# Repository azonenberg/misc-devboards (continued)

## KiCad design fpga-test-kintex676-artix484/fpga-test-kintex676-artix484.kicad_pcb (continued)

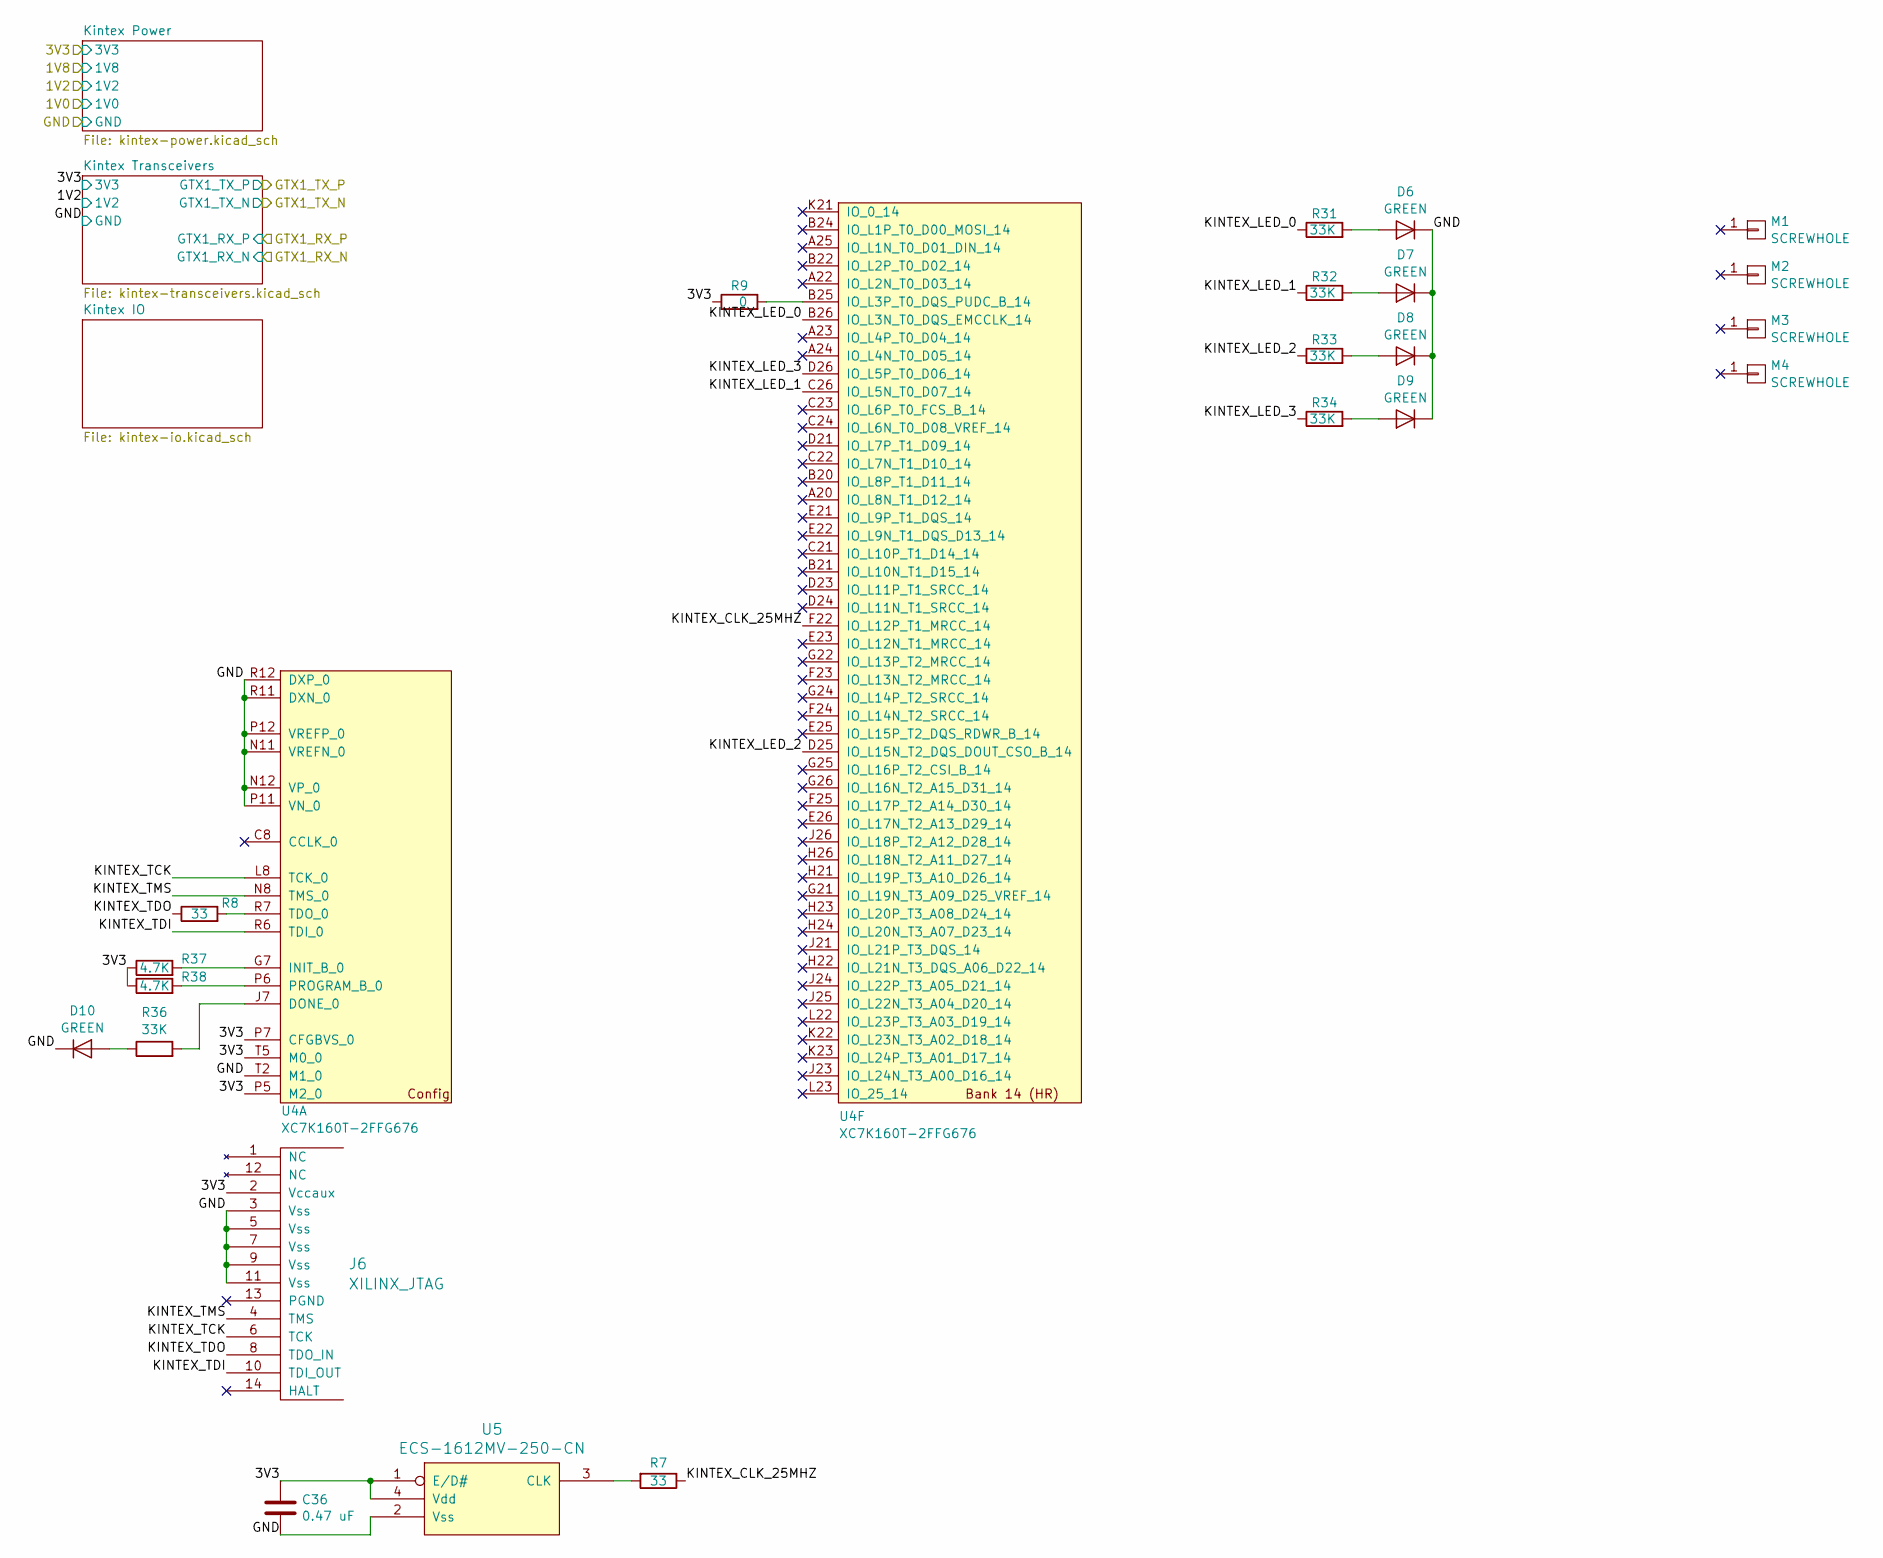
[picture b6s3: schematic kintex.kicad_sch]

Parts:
C36: 0.47 uF; EIA_0402_CAP_NOSILK
D6, D7, D8, D9, D10: GREEN; EIA_0402_LED
J6: XILINX_JTAG; XILINX_JTAG_PTH_MOLEX_0878311420
M1, M2, M3, M4: SCREWHOLE; MECHANICAL_CLEARANCEHOLE_4_40
R7, R8: 33; EIA_0402_RES_NOSILK
R9: 0; EIA_0402_RES_NOSILK
R31, R32, R33, R34, R36: 33K; EIA_0402_RES_NOSILK
R37, R38: 4.7K; EIA_0402_RES_NOSILK
U4: XC7K160T-2FFG676; BGA_676_27x27_FULLARRAY_1MM_FFG676
U5: ECS-1612MV-250-CN; OSCILLATOR_1.6x1.2

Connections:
/GND: C36.2, D6.1 (K), D7.1 (K), D8.1 (K), D9.1 (K), D10.1 (K), J6.3 (Vss), J6.5 (Vss), J6.7 (Vss), J6.9 (Vss), J6.11 (Vss), U4.N11 (VREFN_0), U4.N12 (VP_0), U4.P11 (VN_0), U4.P12 (VREFP_0), U4.R11 (DXN_0), U4.R12 (DXP_0), U4.T2 (M1_0), U5.2 (Vss); also elsewhere on the board
/Kintex FFG676/3V3: C36.1, J6.2 (Vccaux), R9.1, R37.1, R38.1, U4.P5 (M2_0), U4.P7 (CFGBVS_0), U4.T5 (M0_0), U5.1 (E/D#), U5.4 (Vdd); also elsewhere on the board
/Kintex FFG676/KINTEX_CLK_25MHZ: R7.1, U4.F22 (IO_L12P_T1_MRCC_14)
/Kintex FFG676/KINTEX_LED_0: R31.1, U4.B26 (IO_L3N_T0_DQS_EMCCLK_14)
/Kintex FFG676/KINTEX_LED_1: R32.1, U4.C26 (IO_L5N_T0_D07_14)
/Kintex FFG676/KINTEX_LED_2: R33.1, U4.D25 (IO_L15N_T2_DQS_DOUT_CSO_B_14)
/Kintex FFG676/KINTEX_LED_3: R34.1, U4.D26 (IO_L5P_T0_D06_14)
/Kintex FFG676/KINTEX_TCK: J6.6 (TCK), U4.L8 (TCK_0)
/Kintex FFG676/KINTEX_TDI: J6.10 (TDI_OUT), U4.R6 (TDI_0)
/Kintex FFG676/KINTEX_TDO: J6.8 (TDO_IN), R8.1
/Kintex FFG676/KINTEX_TMS: J6.4 (TMS), U4.N8 (TMS_0)
unnamed: D6.2 (A), R31.2
unnamed: D7.2 (A), R32.2
unnamed: D8.2 (A), R33.2
unnamed: D9.2 (A), R34.2
unnamed: D10.2 (A), R36.1
unnamed: R36.2, U4.J7 (DONE_0)
unnamed: R37.2, U4.G7 (INIT_B_0)
unnamed: R38.2, U4.P6 (PROGRAM_B_0)
unnamed: R8.2, U4.R7 (TDO_0)
unnamed: R9.2, U4.B25 (IO_L3P_T0_DQS_PUDC_B_14)
unnamed: R7.2, U5.3 (CLK)

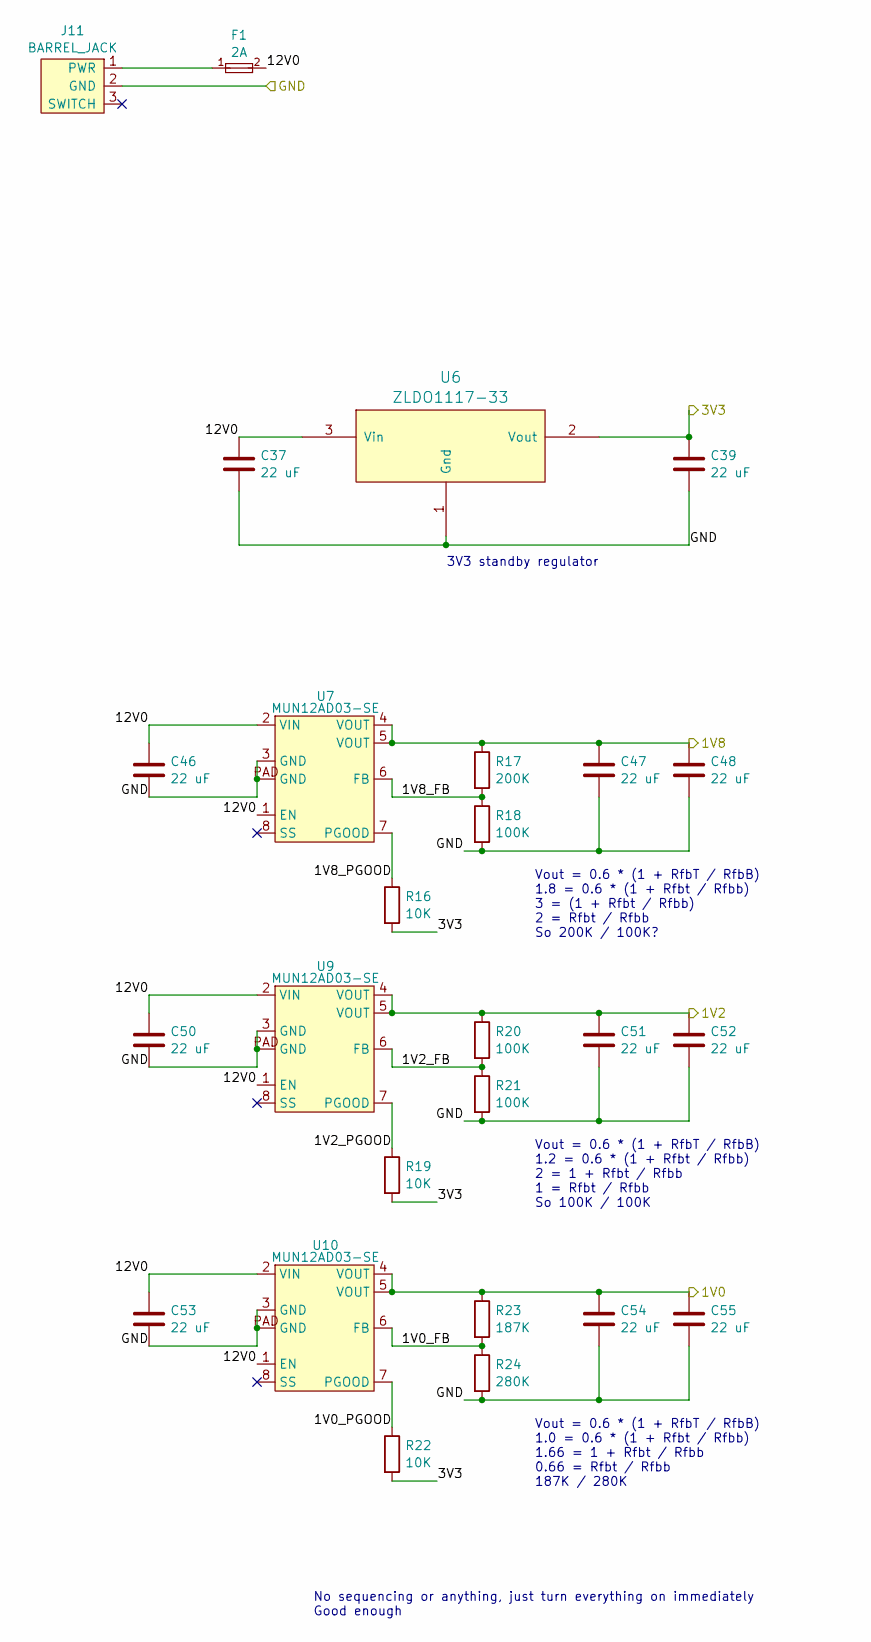
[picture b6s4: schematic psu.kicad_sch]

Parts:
C37, C39, C47, C48, C51, C52, C54, C55: 22 uF; EIA_1210_CAP_NOSILK
C46, C50, C53: 22 uF; EIA_1812_CAP_NOSILK
F1: 2A; EIA_0402_RES_NOSILK
J11: BARREL_JACK; CONN_CUI_PJ-058BH_HIPWR_BARREL_NOSLOT
R16, R19, R22: 10K; EIA_0402_RES_NOSILK
R17: 200K; EIA_0402_RES_NOSILK
R18, R20, R21: 100K; EIA_0402_RES_NOSILK
R23: 187K; EIA_0402_RES_NOSILK
R24: 280K; EIA_0402_RES_NOSILK
U6: ZLDO1117-33; SOT223-4
U7, U9, U10: MUN12AD03-SE; MODULE_CYNTEC_MUN12AD03-SE

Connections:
/1V0: C54.1, C55.1, R23.1, U10.4 (VOUT), U10.5 (VOUT); also elsewhere on the board
/1V2: C51.1, C52.1, R20.1, U9.4 (VOUT), U9.5 (VOUT); also elsewhere on the board
/1V8: C47.1, C48.1, R17.1, U7.4 (VOUT), U7.5 (VOUT); also elsewhere on the board
/3V3: C39.1, R16.2, R19.2, R22.2, U6.2 (Vout); also elsewhere on the board
/GND: C37.2, C39.2, C46.2, C47.2, C48.2, C50.2, C51.2, C52.2, C53.2, C54.2, C55.2, J11.2 (GND), R18.2, R21.2, R24.2, U6.1 (Gnd), U7.3 (GND), U7.PAD (GND), U9.3 (GND), U9.PAD (GND), U10.3 (GND), U10.PAD (GND); also elsewhere on the board
/Power Supply/1V0_FB: R23.2, R24.1, U10.6 (FB)
/Power Supply/1V0_PGOOD: R22.1, U10.7 (PGOOD)
/Power Supply/1V2_FB: R20.2, R21.1, U9.6 (FB)
/Power Supply/1V2_PGOOD: R19.1, U9.7 (PGOOD)
/Power Supply/1V8_FB: R17.2, R18.1, U7.6 (FB)
/Power Supply/1V8_PGOOD: R16.1, U7.7 (PGOOD)
/Power Supply/12V0: C37.1, C46.1, C50.1, C53.1, F1.2, U6.3 (Vin), U7.1 (EN), U7.2 (VIN), U9.1 (EN), U9.2 (VIN), U10.1 (EN), U10.2 (VIN)
unnamed: F1.1, J11.1 (PWR)

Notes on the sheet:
Vout = 0.6 * (1 + RfbT / RfbB) 1.2 = 0.6 * (1 + Rfbt / Rfbb) 2 = 1 + Rfbt / Rfbb 1 = Rfbt / Rfbb So 100K / 100K
Vout = 0.6 * (1 + RfbT / RfbB) 1.8 = 0.6 * (1 + Rfbt / Rfbb) 3 = (1 + Rfbt / Rfbb) 2 = Rfbt / Rfbb So 200K / 100K?
No sequencing or anything, just turn everything on immediately Good enough
3V3 standby regulator
Vout = 0.6 * (1 + RfbT / RfbB) 1.0 = 0.6 * (1 + Rfbt / Rfbb) 1.66 = 1 + Rfbt / Rfbb 0.66 = Rfbt / Rfbb 187K / 280K

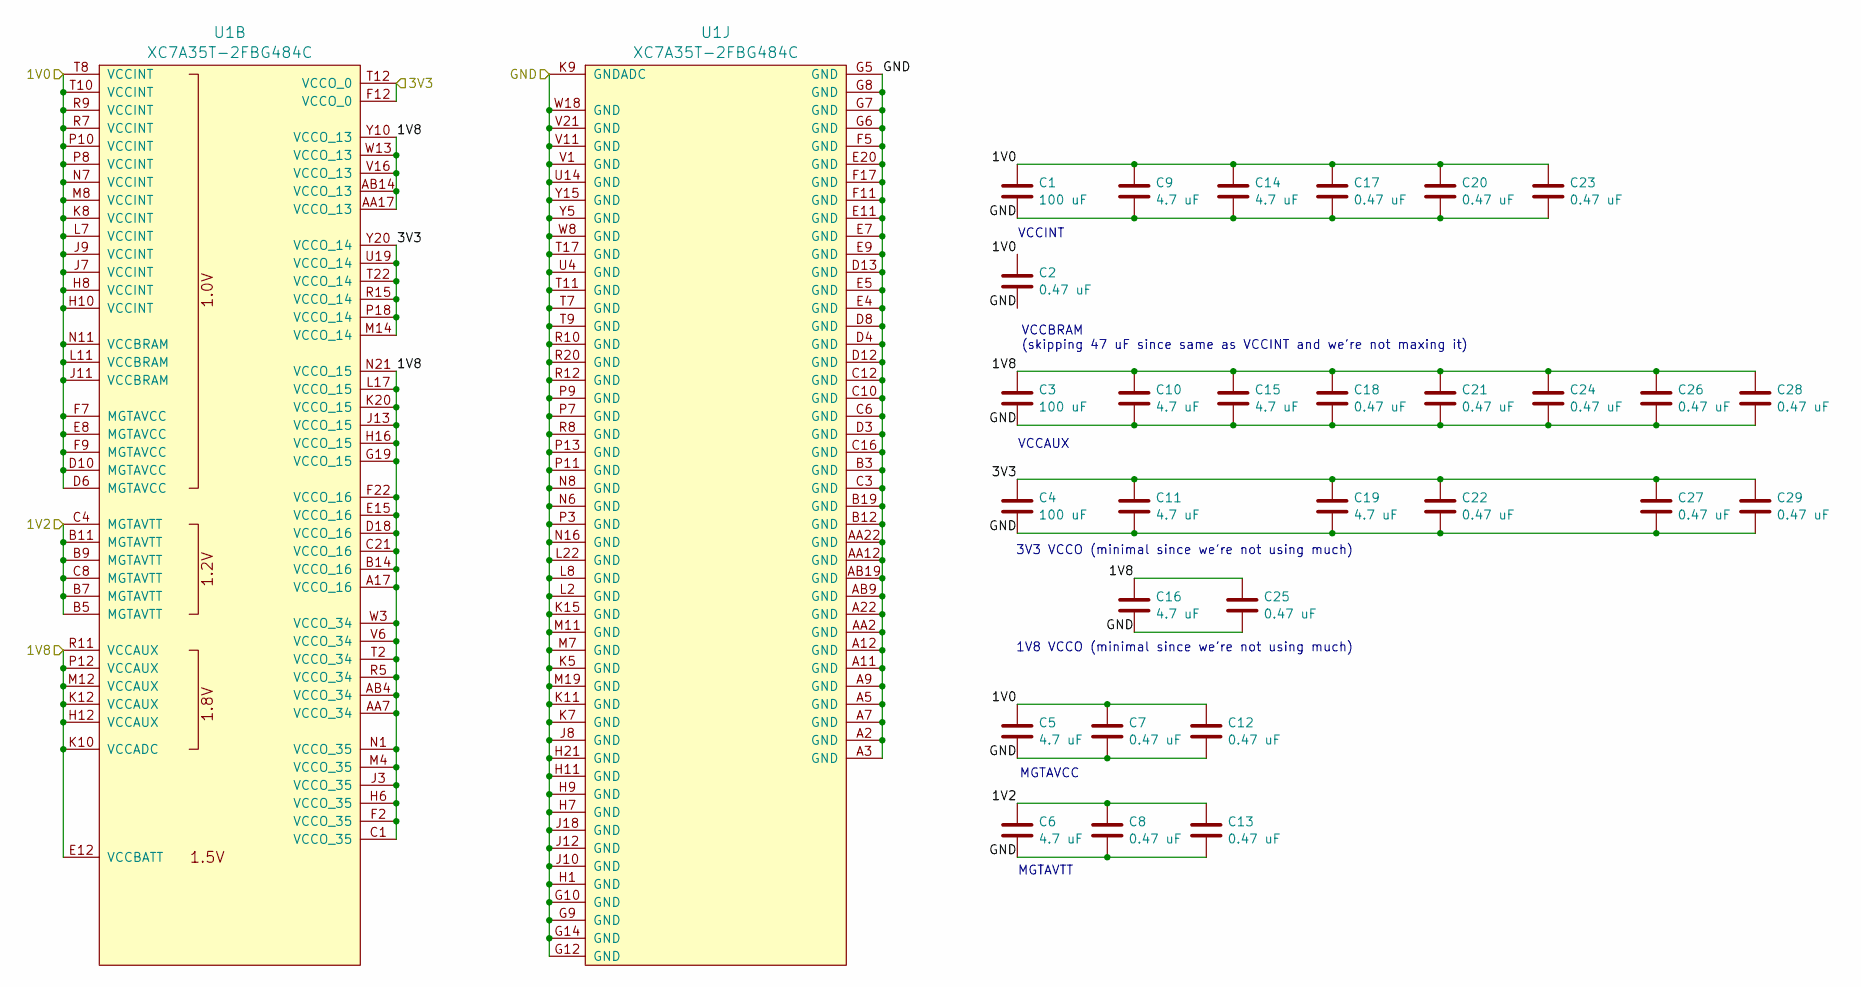
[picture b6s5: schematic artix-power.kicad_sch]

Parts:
C1, C3, C4: 100 uF; EIA_1210_CAP_NOSILK
C2, C7, C8, C12, C13, C17, C18, C20, C21, C22, C23, C24, C25, C26, C27, C28, C29: 0.47 uF; EIA_0402_CAP_NOSILK
C5, C6, C9, C10, C11, C14, C15, C16, C19: 4.7 uF; EIA_0603_CAP_NOSILK
U1: XC7A35T-2FBG484C; BGA_484_22x22_FULLARRAY_1MM

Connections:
/Artix FGG484/1V2: C6.1, C8.1, C13.1, U1.B5 (MGTAVTT), U1.B7 (MGTAVTT), U1.B9 (MGTAVTT), U1.B11 (MGTAVTT), U1.C4 (MGTAVTT), U1.C8 (MGTAVTT); also elsewhere on the board
/Artix FGG484/3V3: C4.1, C11.1, C19.1, C22.1, C27.1, C29.1, U1.F12 (VCCO_0), U1.M14 (VCCO_14), U1.P18 (VCCO_14), U1.R15 (VCCO_14), U1.T12 (VCCO_0), U1.T22 (VCCO_14), U1.U19 (VCCO_14), U1.Y20 (VCCO_14); also elsewhere on the board
/Artix FGG484/Artix Power/1V0: C1.1, C2.1, C5.1, C7.1, C9.1, C12.1, C14.1, C17.1, C20.1, C23.1, U1.D6 (MGTAVCC), U1.D10 (MGTAVCC), U1.E8 (MGTAVCC), U1.F7 (MGTAVCC), U1.F9 (MGTAVCC), U1.H8 (VCCINT), U1.H10 (VCCINT), U1.J7 (VCCINT), U1.J9 (VCCINT), U1.J11 (VCCBRAM), U1.K8 (VCCINT), U1.L7 (VCCINT), U1.L11 (VCCBRAM), U1.M8 (VCCINT), U1.N7 (VCCINT), U1.N11 (VCCBRAM), U1.P8 (VCCINT), U1.P10 (VCCINT), U1.R7 (VCCINT), U1.R9 (VCCINT), U1.T8 (VCCINT), U1.T10 (VCCINT); also elsewhere on the board
/Artix FGG484/Artix Power/1V8: C3.1, C10.1, C15.1, C16.1, C18.1, C21.1, C24.1, C25.1, C26.1, C28.1, U1.A17 (VCCO_16), U1.AA7 (VCCO_34), U1.AA17 (VCCO_13), U1.AB4 (VCCO_34), U1.AB14 (VCCO_13), U1.B14 (VCCO_16), U1.C1 (VCCO_35), U1.C21 (VCCO_16), U1.D18 (VCCO_16), U1.E12 (VCCBATT), U1.E15 (VCCO_16), U1.F2 (VCCO_35), U1.F22 (VCCO_16), U1.G19 (VCCO_15), U1.H6 (VCCO_35), U1.H12 (VCCAUX), U1.H16 (VCCO_15), U1.J3 (VCCO_35), U1.J13 (VCCO_15), U1.K10 (VCCADC), U1.K12 (VCCAUX), U1.K20 (VCCO_15), U1.L17 (VCCO_15), U1.M4 (VCCO_35), U1.M12 (VCCAUX), U1.N1 (VCCO_35), U1.N21 (VCCO_15), U1.P12 (VCCAUX), U1.R5 (VCCO_34), U1.R11 (VCCAUX), U1.T2 (VCCO_34), U1.V6 (VCCO_34), U1.V16 (VCCO_13), U1.W3 (VCCO_34), U1.W13 (VCCO_13), U1.Y10 (VCCO_13); also elsewhere on the board
/GND: C1.2, C2.2, C3.2, C4.2, C5.2, C6.2, C7.2, C8.2, C9.2, C10.2, C11.2, C12.2, C13.2, C14.2, C15.2, C16.2, C17.2, C18.2, C19.2, C20.2, C21.2, C22.2, C23.2, C24.2, C25.2, C26.2, C27.2, C28.2, C29.2, U1.A2 (GND), U1.A3 (GND), U1.A5 (GND), U1.A7 (GND), U1.A9 (GND), U1.A11 (GND), U1.A12 (GND), U1.A22 (GND), U1.AA2 (GND), U1.AA12 (GND), U1.AA22 (GND), U1.AB9 (GND), U1.AB19 (GND), U1.B3 (GND), U1.B12 (GND), U1.B19 (GND), U1.C3 (GND), U1.C6 (GND), U1.C10 (GND), U1.C12 (GND), U1.C16 (GND), U1.D3 (GND), U1.D4 (GND), U1.D8 (GND), U1.D12 (GND), U1.D13 (GND), U1.E4 (GND), U1.E5 (GND), U1.E7 (GND), U1.E9 (GND), U1.E11 (GND), U1.E20 (GND), U1.F5 (GND), U1.F11 (GND), U1.F17 (GND), U1.G5 (GND), U1.G6 (GND), U1.G7 (GND), U1.G8 (GND), U1.G9 (GND), U1.G10 (GND), U1.G12 (GND), U1.G14 (GND), U1.H1 (GND), U1.H7 (GND), U1.H9 (GND), U1.H11 (GND), U1.H21 (GND), U1.J8 (GND), U1.J10 (GND), U1.J12 (GND), U1.J18 (GND), U1.K5 (GND), U1.K7 (GND), U1.K9 (GNDADC), U1.K11 (GND), U1.K15 (GND), U1.L2 (GND), U1.L8 (GND), U1.L22 (GND), U1.M7 (GND), U1.M11 (GND), U1.M19 (GND), U1.N6 (GND), U1.N8 (GND), U1.N16 (GND), U1.P3 (GND), U1.P7 (GND), U1.P9 (GND), U1.P11 (GND), U1.P13 (GND), U1.R8 (GND), U1.R10 (GND), U1.R12 (GND), U1.R20 (GND), U1.T7 (GND), U1.T9 (GND), U1.T11 (GND), U1.T17 (GND), U1.U4 (GND), U1.U14 (GND), U1.V1 (GND), U1.V11 (GND), U1.V21 (GND), U1.W8 (GND), U1.W18 (GND), U1.Y5 (GND), U1.Y15 (GND); also elsewhere on the board

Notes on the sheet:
MGTAVTT
VCCINT
3V3 VCCO (minimal since we're not using much)
VCCAUX
VCCBRAM (skipping 47 uF since same as VCCINT and we're not maxing it)
MGTAVCC
1V8 VCCO (minimal since we're not using much)

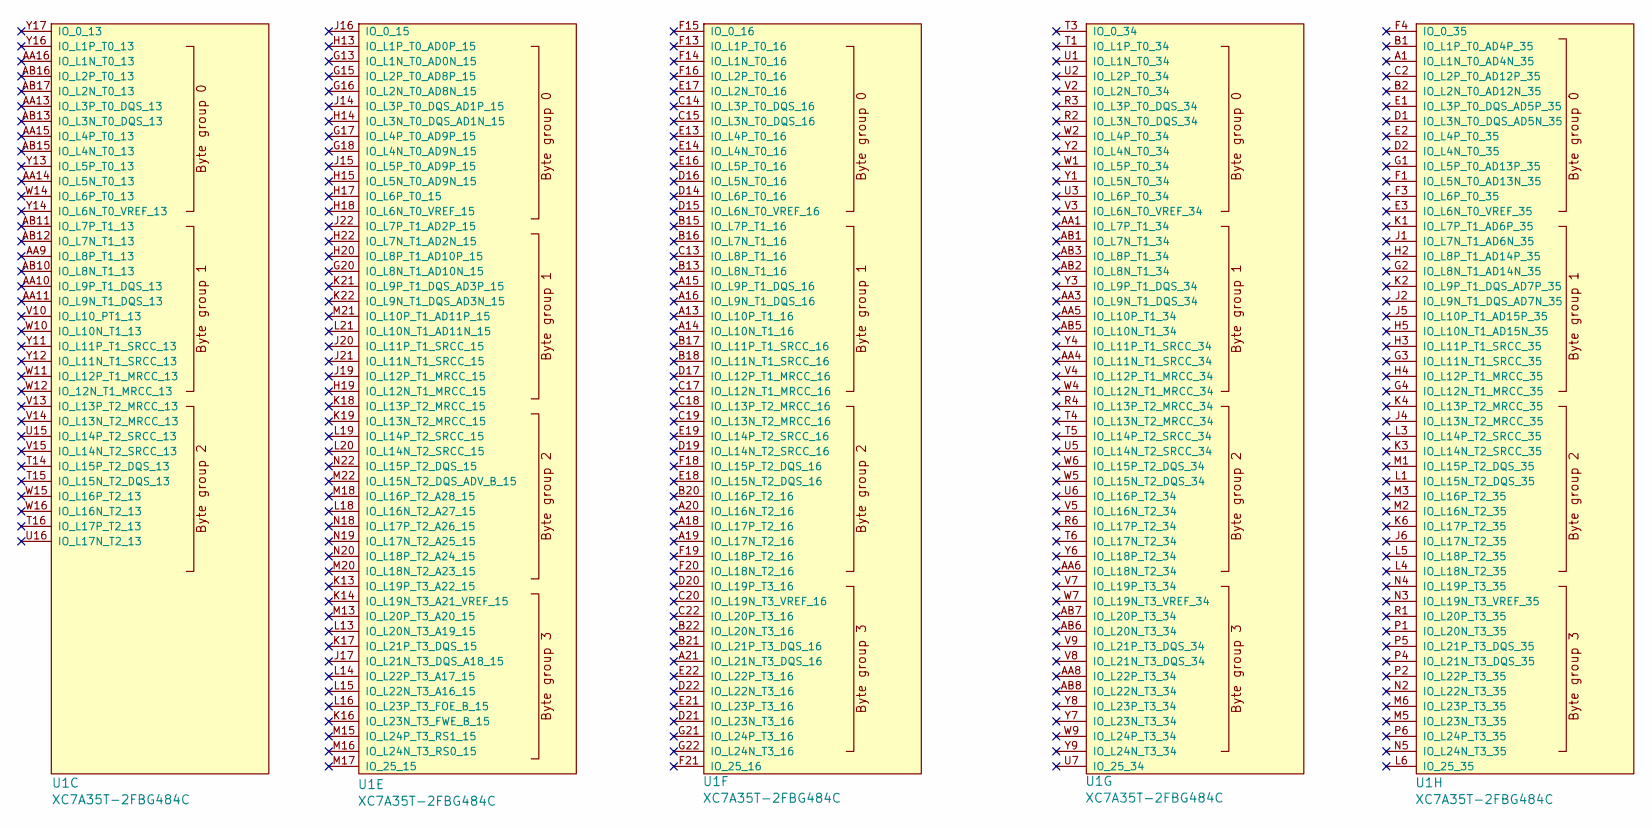
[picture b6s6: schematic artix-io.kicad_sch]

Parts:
U1: XC7A35T-2FBG484C; BGA_484_22x22_FULLARRAY_1MM

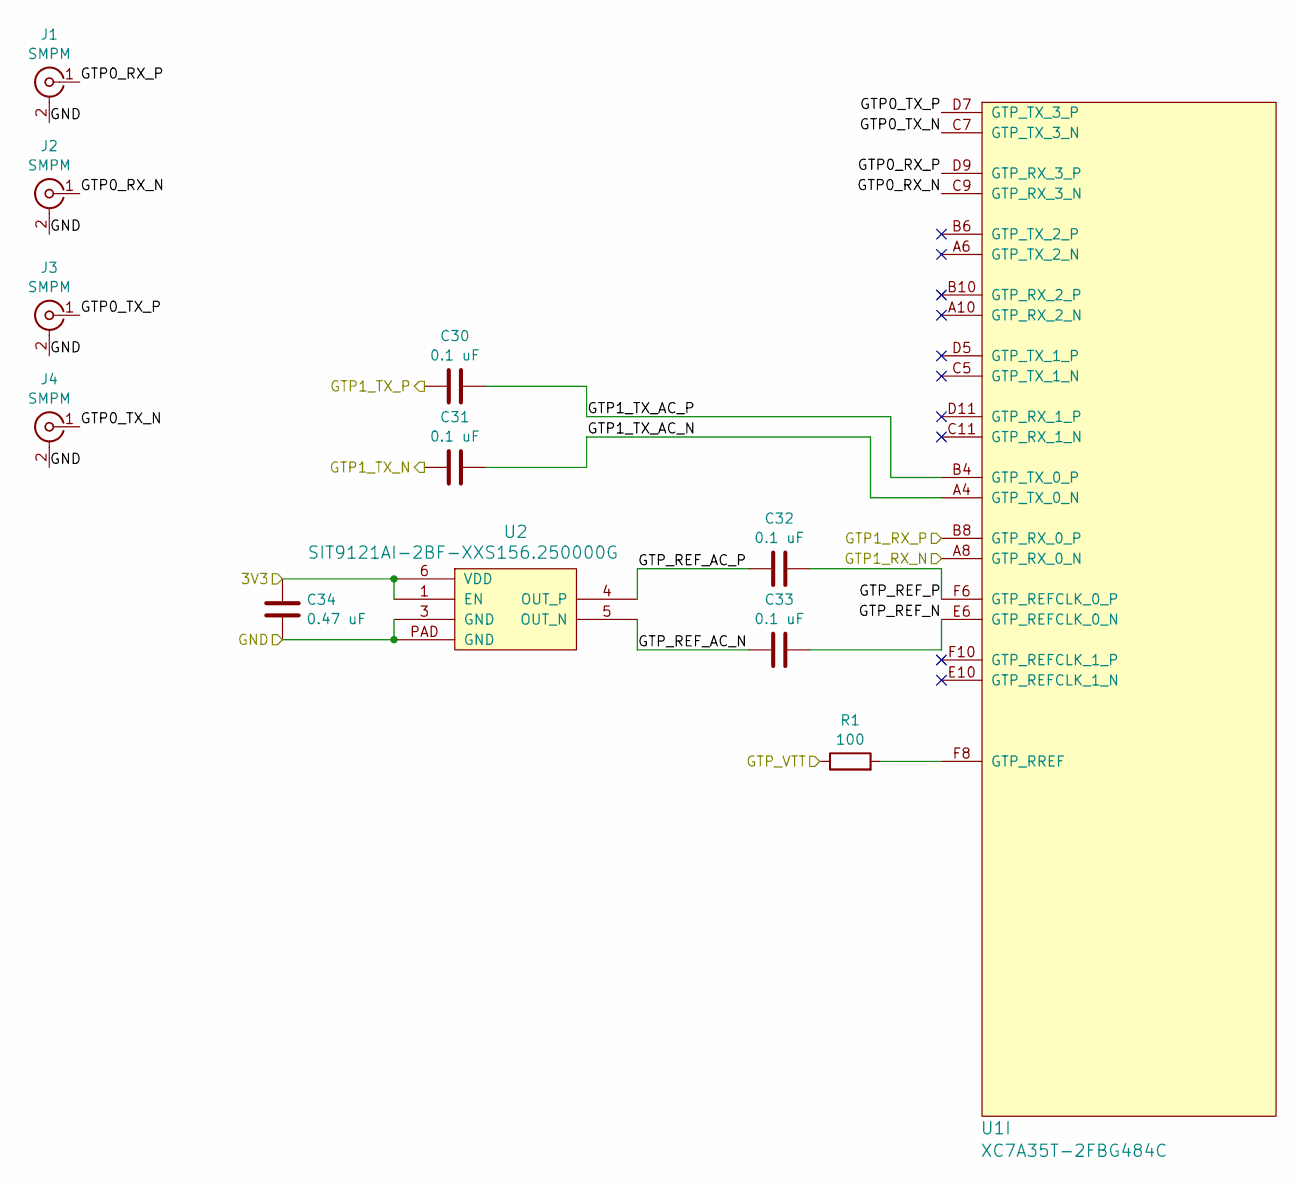
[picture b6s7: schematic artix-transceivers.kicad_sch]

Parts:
C30, C31, C32, C33: 0.1 uF; EIA_0402_CAP_NOSILK
C34: 0.47 uF; EIA_0402_CAP_NOSILK
J1, J2, J3, J4: SMPM; CONN_SMPM_AMPHENOL_C925-197J-51PT
R1: 100; EIA_0402_RES_NOSILK
U1: XC7A35T-2FBG484C; BGA_484_22x22_FULLARRAY_1MM
U2: SIT9121AI-2BF-XXS156.250000G; OSCILLATOR_LVDS_3.2x2.5

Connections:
/Artix FGG484/1V2: R1.1; also elsewhere on the board
/Artix FGG484/3V3: C34.1, U2.1 (EN), U2.6 (VDD); also elsewhere on the board
/Artix FGG484/ARTIX_RX_N: U1.A8 (GTP_RX_0_N); also elsewhere on the board
/Artix FGG484/ARTIX_RX_P: U1.B8 (GTP_RX_0_P); also elsewhere on the board
/Artix FGG484/ARTIX_TX_N: C31.1; also elsewhere on the board
/Artix FGG484/ARTIX_TX_P: C30.1; also elsewhere on the board
/Artix FGG484/Artix Transceivers/GTP0_RX_N: J2.1 (In), U1.C9 (GTP_RX_3_N)
/Artix FGG484/Artix Transceivers/GTP0_RX_P: J1.1 (In), U1.D9 (GTP_RX_3_P)
/Artix FGG484/Artix Transceivers/GTP0_TX_N: J4.1 (In), U1.C7 (GTP_TX_3_N)
/Artix FGG484/Artix Transceivers/GTP0_TX_P: J3.1 (In), U1.D7 (GTP_TX_3_P)
/Artix FGG484/Artix Transceivers/GTP1_TX_AC_N: C31.2, U1.A4 (GTP_TX_0_N)
/Artix FGG484/Artix Transceivers/GTP1_TX_AC_P: C30.2, U1.B4 (GTP_TX_0_P)
/Artix FGG484/Artix Transceivers/GTP_REF_AC_N: C33.1, U2.5 (OUT_N)
/Artix FGG484/Artix Transceivers/GTP_REF_AC_P: C32.1, U2.4 (OUT_P)
/Artix FGG484/Artix Transceivers/GTP_REF_N: C33.2, U1.E6 (GTP_REFCLK_0_N)
/Artix FGG484/Artix Transceivers/GTP_REF_P: C32.2, U1.F6 (GTP_REFCLK_0_P)
/GND: C34.2, J1.2 (Ext), J2.2 (Ext), J3.2 (Ext), J4.2 (Ext), U2.3 (GND), U2.PAD (GND); also elsewhere on the board
unnamed: R1.2, U1.F8 (GTP_RREF)

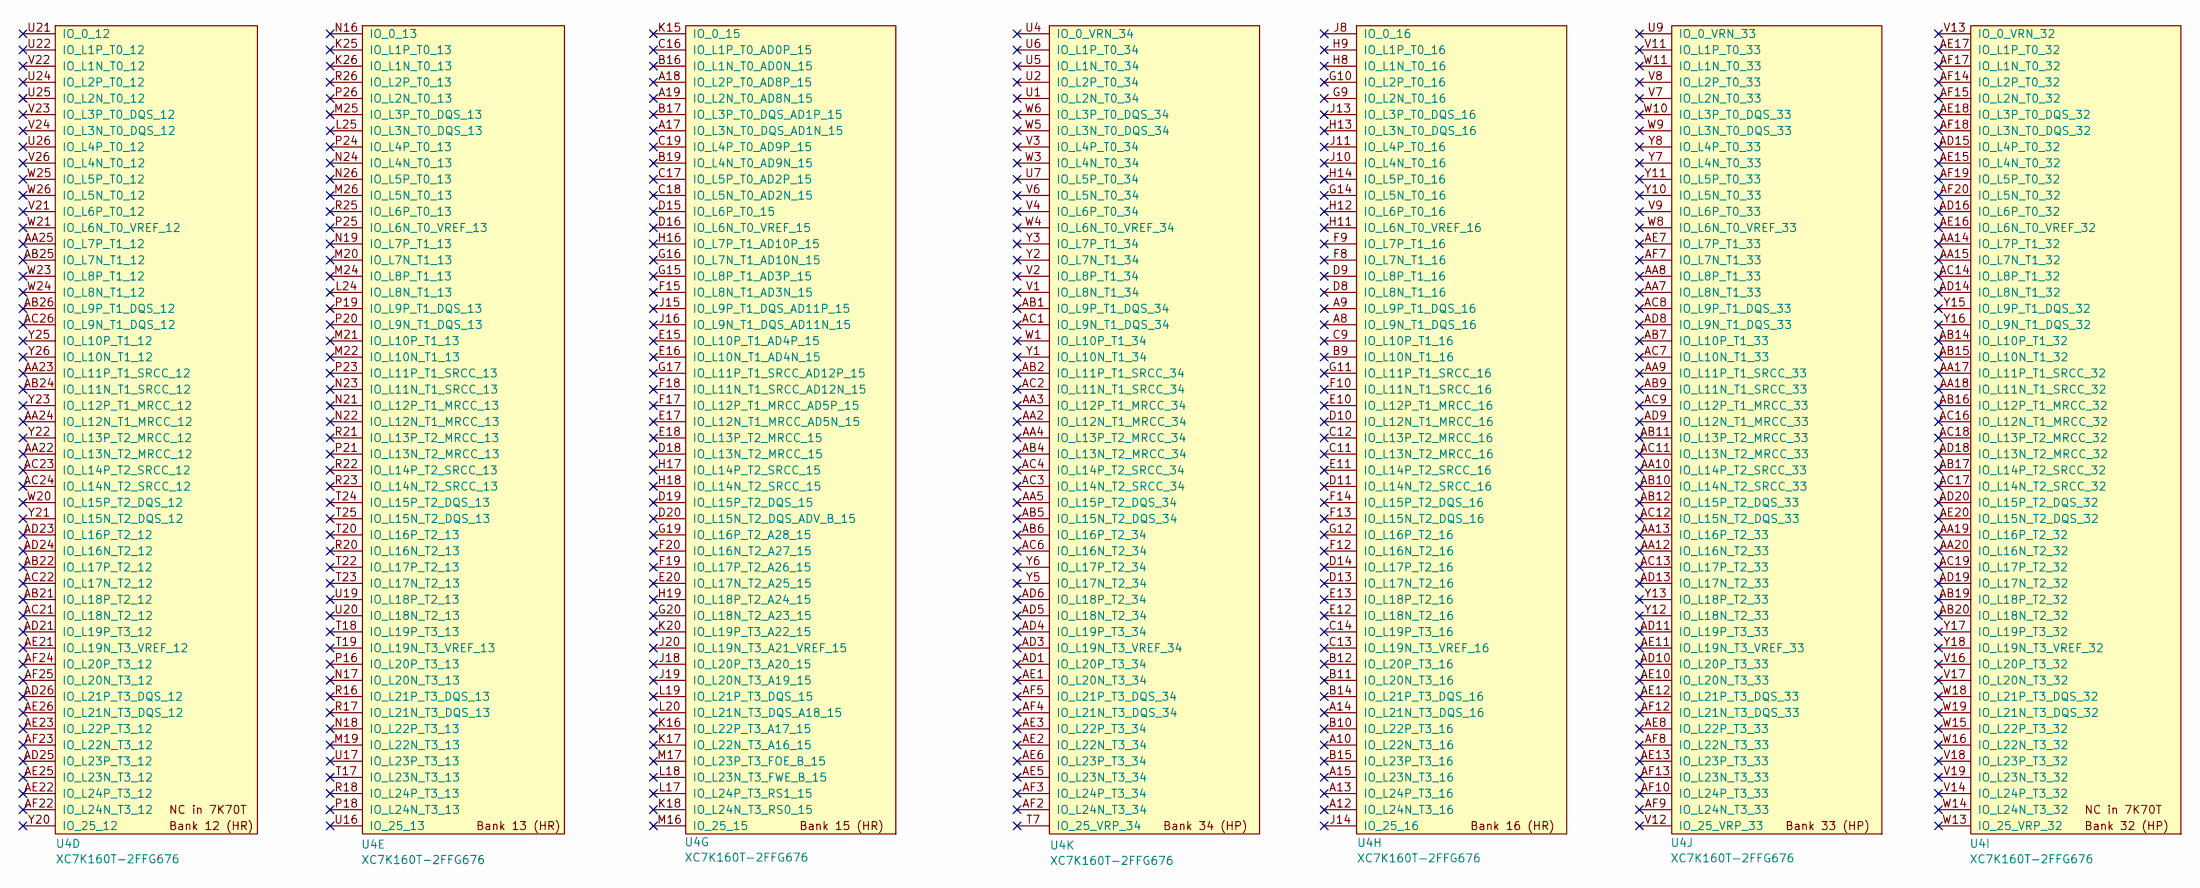
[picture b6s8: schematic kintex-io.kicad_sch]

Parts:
U4: XC7K160T-2FFG676; BGA_676_27x27_FULLARRAY_1MM_FFG676

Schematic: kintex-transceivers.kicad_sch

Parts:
C40, C41, C42, C43, C44, C45, C67, C68, C69, C70, C71, C72, C73, C74, C76, C77, C79, C80: 0.1 uF; EIA_0402_CAP_NOSILK
C75, C78: 0.47 uF; EIA_0402_CAP_NOSILK
J7, J8, J9, J10: SMPM; CONN_SMPM_AMPHENOL_C925-197J-51PT
R35: 100; EIA_0402_RES_NOSILK
U4: XC7K160T-2FFG676; BGA_676_27x27_FULLARRAY_1MM_FFG676
U8, U11: SIT9121AI-2BF-XXS156.250000G; OSCILLATOR_LVDS_3.2x2.5

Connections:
/Artix FGG484/ARTIX_RX_N: C41.1; also elsewhere on the board
/Artix FGG484/ARTIX_RX_P: C40.1; also elsewhere on the board
/Artix FGG484/ARTIX_TX_N: U4.R4 (MGTXRXP0_115); also elsewhere on the board
/Artix FGG484/ARTIX_TX_P: U4.R3 (MGTXRXN0_115); also elsewhere on the board
/GND: C75.2, C78.2, J7.2 (Ext), J8.2 (Ext), J9.2 (Ext), J10.2 (Ext), U8.3 (GND), U8.PAD (GND), U11.3 (GND), U11.PAD (GND); also elsewhere on the board
/Kintex FFG676/1V2: R35.2, U4.M5 (MGTAVTTRCAL_115); also elsewhere on the board
/Kintex FFG676/3V3: C75.1, C78.1, U8.1 (EN), U8.6 (VDD), U11.1 (EN), U11.6 (VDD); also elsewhere on the board
/Kintex FFG676/Kintex Transceivers/GTX0_RX_N: J8.1 (In), U4.B5 (MGTXRXN3_116)
/Kintex FFG676/Kintex Transceivers/GTX0_RX_P: J7.1 (In), U4.B6 (MGTXRXP3_116)
/Kintex FFG676/Kintex Transceivers/GTX0_TX_N: J10.1 (In), U4.A3 (MGTXTXN3_116)
/Kintex FFG676/Kintex Transceivers/GTX0_TX_P: J9.1 (In), U4.A4 (MGTXTXP3_116)
/Kintex FFG676/Kintex Transceivers/GTX1_REF_AC_N: C77.1, U8.5 (OUT_N)
/Kintex FFG676/Kintex Transceivers/GTX1_REF_AC_P: C76.1, U8.4 (OUT_P)
/Kintex FFG676/Kintex Transceivers/GTX1_TX_AC_N: C41.2, U4.P1 (MGTXTXN0_115)
/Kintex FFG676/Kintex Transceivers/GTX1_TX_AC_P: C40.2, U4.P2 (MGTXTXP0_115)
/Kintex FFG676/Kintex Transceivers/GTX2_REF_AC_N: C80.1, U11.5 (OUT_N)
/Kintex FFG676/Kintex Transceivers/GTX2_REF_AC_P: C79.1, U11.4 (OUT_P)
/Kintex FFG676/Kintex Transceivers/GTX2_TX_AC_N: C43.2, U4.B1 (MGTXTXN2_116)
/Kintex FFG676/Kintex Transceivers/GTX2_TX_AC_P: C42.2, U4.B2 (MGTXTXP2_116)
/Kintex FFG676/Kintex Transceivers/GTX2_TX_N: C43.1, U4.C3 (MGTXRXN2_116)
/Kintex FFG676/Kintex Transceivers/GTX2_TX_P: C42.1, U4.C4 (MGTXRXP2_116)
/Kintex FFG676/Kintex Transceivers/GTX3_TX_AC_N: C45.2, U4.D1 (MGTXTXN1_116)
/Kintex FFG676/Kintex Transceivers/GTX3_TX_AC_P: C44.2, U4.D2 (MGTXTXP1_116)
/Kintex FFG676/Kintex Transceivers/GTX3_TX_N: C45.1, U4.E3 (MGTXRXN1_116)
/Kintex FFG676/Kintex Transceivers/GTX3_TX_P: C44.1, U4.E4 (MGTXRXP1_116)
/Kintex FFG676/Kintex Transceivers/GTX4_TX_AC_N: C68.2, U4.H1 (MGTXTXN3_115)
/Kintex FFG676/Kintex Transceivers/GTX4_TX_AC_P: C67.2, U4.H2 (MGTXTXP3_115)
/Kintex FFG676/Kintex Transceivers/GTX4_TX_N: C68.1, U4.J4 (MGTXRXP3_115)
/Kintex FFG676/Kintex Transceivers/GTX4_TX_P: C67.1, U4.J3 (MGTXRXN3_115)
/Kintex FFG676/Kintex Transceivers/GTX5_TX_AC_N: C72.2, U4.K1 (MGTXTXN2_115)
/Kintex FFG676/Kintex Transceivers/GTX5_TX_AC_P: C71.2, U4.K2 (MGTXTXP2_115)
/Kintex FFG676/Kintex Transceivers/GTX5_TX_N: C72.1, U4.L4 (MGTXRXP2_115)
/Kintex FFG676/Kintex Transceivers/GTX5_TX_P: C71.1, U4.L3 (MGTXRXN2_115)
/Kintex FFG676/Kintex Transceivers/GTX6_TX_AC_N: C70.2, U4.M1 (MGTXTXN1_115)
/Kintex FFG676/Kintex Transceivers/GTX6_TX_AC_P: C69.2, U4.M2 (MGTXTXP1_115)
/Kintex FFG676/Kintex Transceivers/GTX6_TX_N: C70.1, U4.N4 (MGTXRXP1_115)
/Kintex FFG676/Kintex Transceivers/GTX6_TX_P: C69.1, U4.N3 (MGTXRXN1_115)
/Kintex FFG676/Kintex Transceivers/GTX7_TX_AC_N: C74.2, U4.F1 (MGTXTXN0_116)
/Kintex FFG676/Kintex Transceivers/GTX7_TX_AC_P: C73.2, U4.F2 (MGTXTXP0_116)
/Kintex FFG676/Kintex Transceivers/GTX7_TX_N: C74.1, U4.G3 (MGTXRXN0_116)
/Kintex FFG676/Kintex Transceivers/GTX7_TX_P: C73.1, U4.G4 (MGTXRXP0_116)
/Kintex FFG676/Kintex Transceivers/GTX_REF1_N: C77.2, U4.D5 (MGTREFCLK0N_116)
/Kintex FFG676/Kintex Transceivers/GTX_REF1_P: C76.2, U4.D6 (MGTREFCLK0P_116)
/Kintex FFG676/Kintex Transceivers/GTX_REF2_N: C80.2, U4.H5 (MGTREFCLK0N_115)
/Kintex FFG676/Kintex Transceivers/GTX_REF2_P: C79.2, U4.H6 (MGTREFCLK0P_115)
unnamed: R35.1, U4.M6 (MGTRREF_115)

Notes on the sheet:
Flip

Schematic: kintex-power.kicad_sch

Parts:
C38, C49: 330 uF; EIA_1210_CAP_NOSILK
C56: 100 uF; EIA_1210_CAP_NOSILK
C57, C58, C59, C64, C65, C66: 4.7 uF; EIA_0603_CAP_NOSILK
C60, C61, C62, C63: 47 uF; EIA_1210_CAP_NOSILK
U4: XC7K160T-2FFG676; BGA_676_27x27_FULLARRAY_1MM_FFG676

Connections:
/GND: C38.2, C49.2, C56.2, C57.2, C58.2, C59.2, C60.2, C61.2, C62.2, C63.2, C64.2, C65.2, C66.2, U4.A1 (GND), U4.A2 (GND), U4.A5 (GND), U4.A6 (GND), U4.A7 (GND), U4.A16 (GND), U4.A26 (GND), U4.AA6 (GND), U4.AA16 (GND), U4.AA26 (GND), U4.AB3 (GND), U4.AB13 (GND), U4.AB23 (GND), U4.AC10 (GND), U4.AC20 (GND), U4.AD7 (GND), U4.AD17 (GND), U4.AE4 (GND), U4.AE14 (GND), U4.AE24 (GND), U4.AF1 (GND), U4.AF11 (GND), U4.AF21 (GND), U4.B4 (GND), U4.B7 (GND), U4.B13 (GND), U4.B23 (GND), U4.C1 (GND), U4.C5 (GND), U4.C7 (GND), U4.C10 (GND), U4.C20 (GND), U4.D4 (GND), U4.D7 (GND), U4.D17 (GND), U4.E1 (GND), U4.E2 (GND), U4.E5 (GND), U4.E7 (GND), U4.E14 (GND), U4.E24 (GND), U4.F3 (GND), U4.F4 (GND), U4.F7 (GND), U4.F11 (GND), U4.F21 (GND), U4.G1 (GND), U4.G5 (GND), U4.G8 (GND), U4.G18 (GND), U4.H4 (GND), U4.H7 (GND), U4.H15 (GND), U4.H25 (GND), U4.J1 (GND), U4.J2 (GND), U4.J5 (GND), U4.J12 (GND), U4.J22 (GND), U4.K3 (GND), U4.K4 (GND), U4.K7 (GND), U4.K9 (GND), U4.K11 (GND), U4.K13 (GND), U4.K19 (GND), U4.L1 (GND), U4.L5 (GND), U4.L10 (GND), U4.L12 (GND), U4.L14 (GND), U4.L16 (GND), U4.L26 (GND), U4.M4 (GND), U4.M7 (GND), U4.M9 (GND), U4.M11 (GNDADC_0), U4.M13 (GND), U4.M15 (GND), U4.M23 (GND), U4.N1 (GND), U4.N2 (GND), U4.N5 (GND), U4.N7 (GND), U4.N10 (GND), U4.N14 (GND), U4.N20 (GND), U4.P3 (GND), U4.P4 (GND), U4.P9 (GND), U4.P13 (GND), U4.P15 (GND), U4.P17 (GND), U4.R1 (GND), U4.R2 (GND), U4.R5 (GND), U4.R8 (GND), U4.R10 (GND), U4.R14 (GND), U4.R24 (GND), U4.T1 (GND), U4.T3 (GND), U4.T4 (GND), U4.T9 (GND), U4.T11 (GND), U4.T13 (GND), U4.T15 (GND), U4.T21 (GND), U4.U8 (GND), U4.U10 (GND), U4.U12 (GND), U4.U14 (GND), U4.U18 (GND), U4.V5 (GND), U4.V15 (GND), U4.V25 (GND), U4.W2 (GND), U4.W12 (GND), U4.W22 (GND), U4.Y9 (GND), U4.Y19 (GND); also elsewhere on the board
/Kintex FFG676/1V2: C65.1, U4.B3 (MGTAVTT), U4.C2 (MGTAVTT), U4.D3 (MGTAVTT), U4.G2 (MGTAVTT), U4.H3 (MGTAVTT), U4.L2 (MGTAVTT), U4.M3 (MGTAVTT); also elsewhere on the board
/Kintex FFG676/3V3: C63.1, U4.A21 (VCCO_14), U4.C25 (VCCO_14), U4.D22 (VCCO_14), U4.F26 (VCCO_14), U4.G23 (VCCO_14), U4.L7 (VCCO_0), U4.L21 (VCCO_14), U4.T6 (VCCO_0); also elsewhere on the board
/Kintex FFG676/Kintex Power/1V0: C38.1, C49.1, C56.1, C57.1, C58.1, C59.1, C64.1, U4.C6 (MGTAVCC), U4.E6 (MGTAVCC), U4.G6 (MGTAVCC), U4.J6 (MGTAVCC), U4.J9 (VCCINT), U4.K8 (VCCINT), U4.K10 (VCCINT), U4.K12 (VCCINT), U4.K14 (VCCINT), U4.L6 (MGTAVCC), U4.L9 (VCCINT), U4.L13 (VCCINT), U4.L15 (VCCINT), U4.M8 (VCCINT), U4.M14 (VCCINT), U4.N9 (VCCINT), U4.N13 (VCCBRAM), U4.N15 (VCCINT), U4.P14 (VCCINT), U4.R13 (VCCBRAM), U4.R15 (VCCINT), U4.T12 (VCCBRAM), U4.T14 (VCCINT), U4.U13 (VCCBRAM), U4.U15 (VCCINT); also elsewhere on the board
/Kintex FFG676/Kintex Power/1V8: C60.1, C61.1, C62.1, C66.1, U4.A11 (VCCO_16), U4.AA1 (VCCO_34), U4.AA11 (VCCO_33), U4.AA21 (VCCO_12), U4.AB8 (VCCO_33), U4.AB18 (VCCO_32), U4.AC5 (VCCO_34), U4.AC15 (VCCO_32), U4.AC25 (VCCO_12), U4.AD2 (VCCO_34), U4.AD12 (VCCO_33), U4.AD22 (VCCO_12), U4.AE9 (VCCO_33), U4.AE19 (VCCO_32), U4.AF6 (VCCO_34), U4.AF16 (VCCO_32), U4.AF26 (VCCO_12), U4.B8 (VCCO_16), U4.B18 (VCCO_15), U4.C15 (VCCO_16), U4.D12 (VCCO_16), U4.E8 (VCCBATT_0), U4.E9 (VCCO_16), U4.E19 (VCCO_15), U4.F16 (VCCO_15), U4.G13 (VCCO_16), U4.H10 (VCCO_16), U4.H20 (VCCO_15), U4.J17 (VCCO_15), U4.K24 (VCCO_13), U4.L11 (VCCAUX), U4.M10 (VCCAUX), U4.M12 (VCCADC_0), U4.M18 (VCCO_15), U4.N6 (MGTVCCAUX), U4.N25 (VCCO_13), U4.P8 (VCCAUX_IO_G0), U4.P10 (VCCAUX), U4.P22 (VCCO_13), U4.R9 (VCCAUX_IO_G0), U4.R19 (VCCO_13), U4.T8 (VCCAUX_IO_G0), U4.T10 (VCCAUX), U4.T16 (VCCO_13), U4.T26 (VCCO_13), U4.U3 (VCCO_34), U4.U11 (VCCAUX), U4.U23 (VCCO_12), U4.V10 (VCCO_33), U4.V20 (VCCO_12), U4.W7 (VCCO_33), U4.W17 (VCCO_32), U4.Y4 (VCCO_34), U4.Y14 (VCCO_32), U4.Y24 (VCCO_12); also elsewhere on the board

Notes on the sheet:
GTX rails
VCCO 3.3V
VCCINT / VCCBRAM
VCCAUX / VCCAUX_IO / VCCO 1.8V
